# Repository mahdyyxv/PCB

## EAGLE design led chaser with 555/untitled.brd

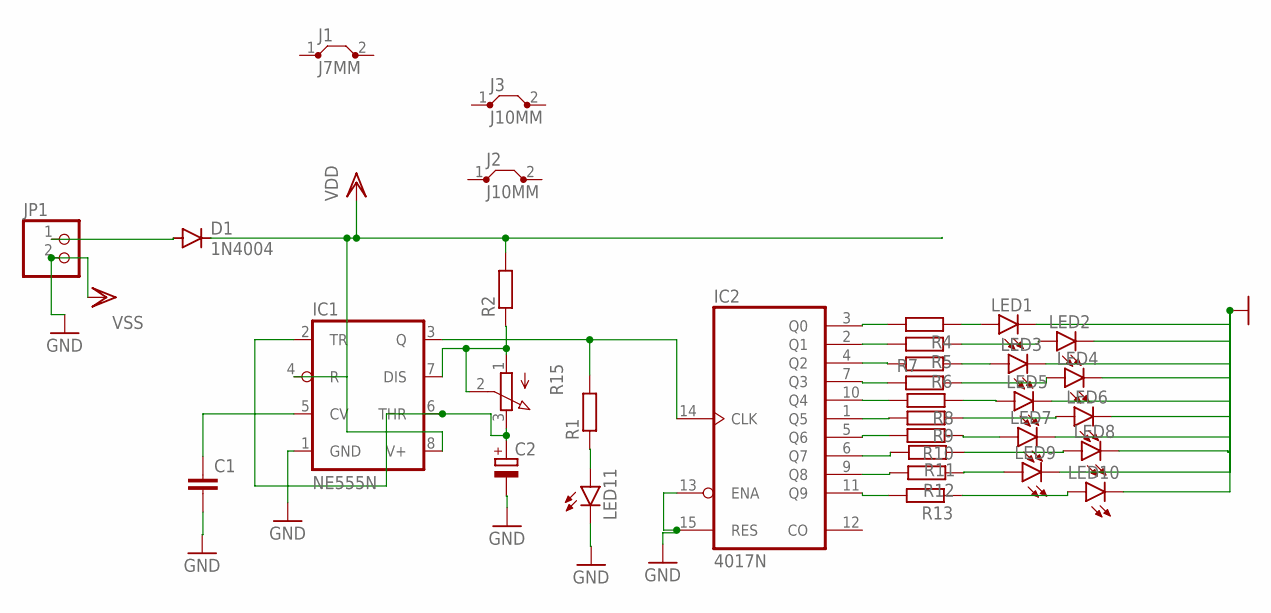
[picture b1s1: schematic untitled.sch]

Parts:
C1: C-EU025-024X044; C025-024X044
C2: CPOL-EUE2.5-5; E2,5-5
D1: 1N4004; DO41-10
IC1: NE555N; DIL08
IC2: 4017N; DIL16
J1: J7MM; 07
J2, J3: J10MM; 10
JP1: PINHD-1X2; 1X02
LED1, LED2, LED3, LED4, LED5, LED6, LED7, LED8, LED9, LED10, LED11: LED5MM
R1, R2, R4, R5, R6, R7, R8, R9, R10, R11, R12, R13: R-EU_0207/7; 0207/7
R15: 3RP/1610N

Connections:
GND: C1.2, C2.-, IC1.1 (GND), IC2.13 (ENA), IC2.15 (RES), LED1.K (C), LED2.K (C), LED3.K (C), LED4.K (C), LED5.K (C), LED6.K (C), LED7.K (C), LED8.K (C), LED9.K (C), LED10.K (C), LED11.K (C)
unnamed: LED11.A, R1.1
unnamed: C1.1, IC1.5 (CV)
unnamed: D1.A, JP1.1
unnamed: IC2.3 (Q0), R4.2
unnamed: C2.+, IC1.2 (TR), IC1.6 (THR), R15.3 (E)
unnamed: IC1.7 (DIS), R2.1, R15.1 (A), R15.2 (S)
unnamed: IC1.3 (Q), IC2.14 (CLK), R1.2
unnamed: LED1.A, R4.1
unnamed: LED2.A, R5.1
unnamed: IC2.2 (Q1), R5.2
unnamed: IC2.4 (Q2), R6.2
unnamed: LED3.A, R6.1
unnamed: IC2.7 (Q3), R7.1
unnamed: IC2.10 (Q4), R8.2
unnamed: IC2.1 (Q5), R9.2
unnamed: IC2.5 (Q6), R10.2
unnamed: IC2.6 (Q7), R11.2
unnamed: IC2.9 (Q8), R12.2
unnamed: IC2.11 (Q9), R13.2
unnamed: LED10.A, R13.1
unnamed: LED9.A, R12.1
unnamed: LED8.A, R11.1
unnamed: LED7.A, R10.1
unnamed: LED6.A, R9.1
unnamed: LED5.A, R8.1
unnamed: LED4.A, R7.2
VDD: D1.C, IC1.4 (R), IC1.8 (V+), IC2.16 (VDD), R2.2
VSS: IC2.8 (VSS), JP1.2

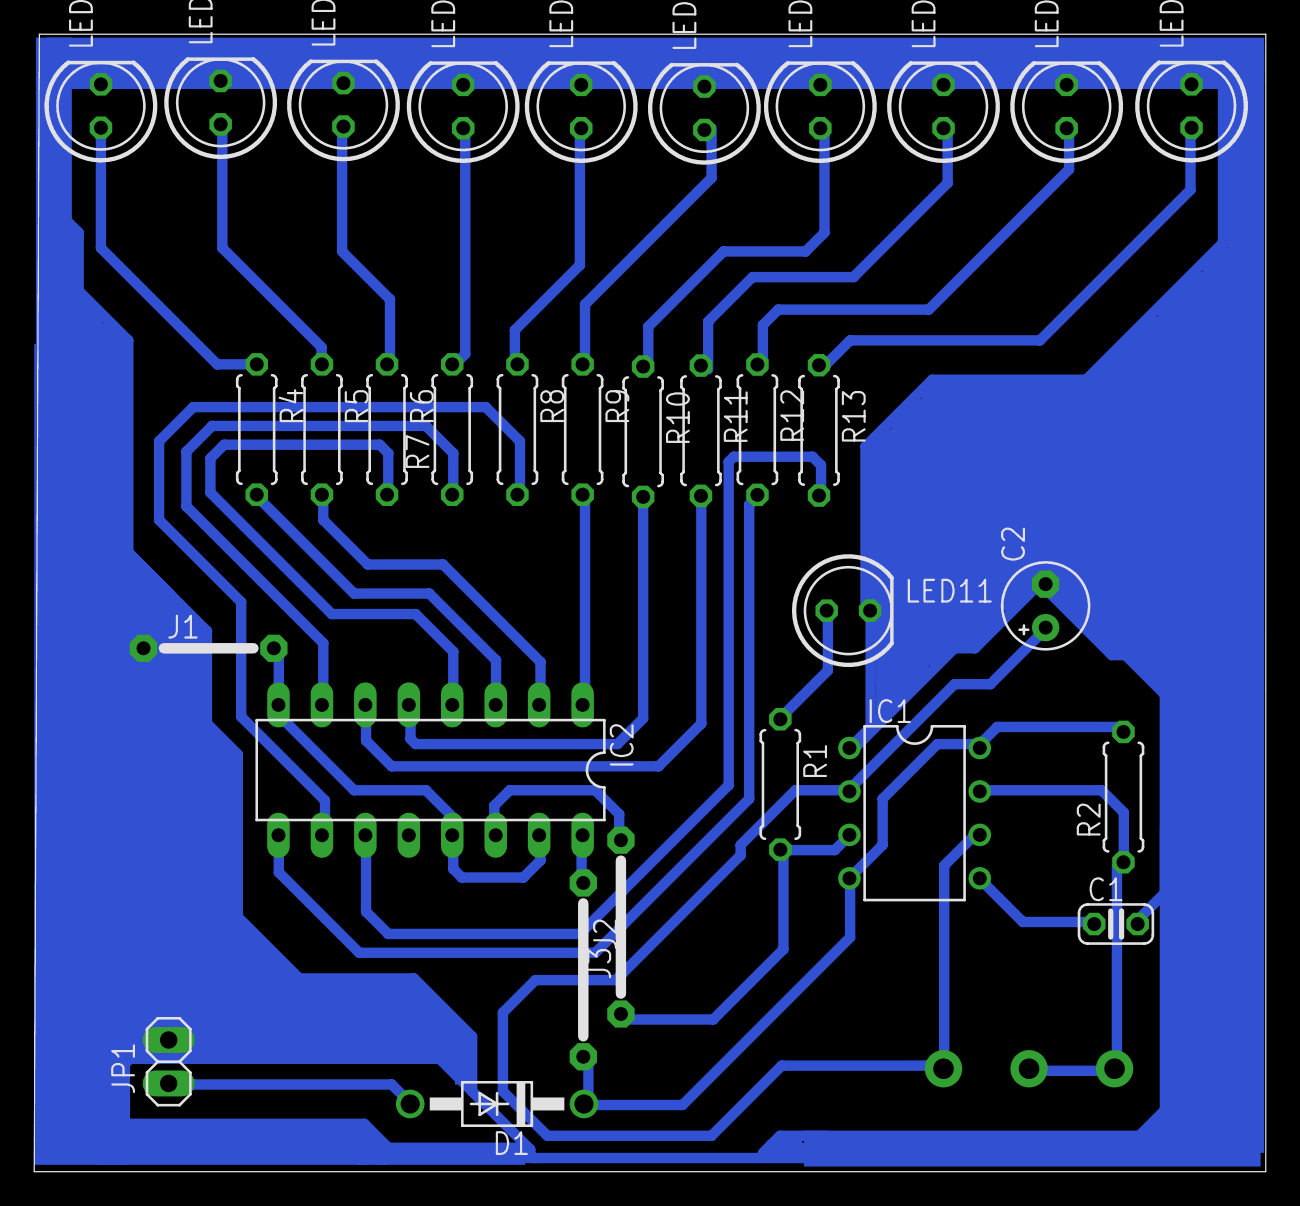
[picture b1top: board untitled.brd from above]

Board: 2 copper layers, 72.0 x 66.5 mm, 33 parts (1 on the bottom side), 29 nets.
